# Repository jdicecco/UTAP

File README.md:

# UTAP
Undersea Technology Apprentice Program Python code

Program requires modules from the Adafruit CircuitPython libraries.  Also incorporates a snippet from the joystick.py interface modified to be Python3 compatible.

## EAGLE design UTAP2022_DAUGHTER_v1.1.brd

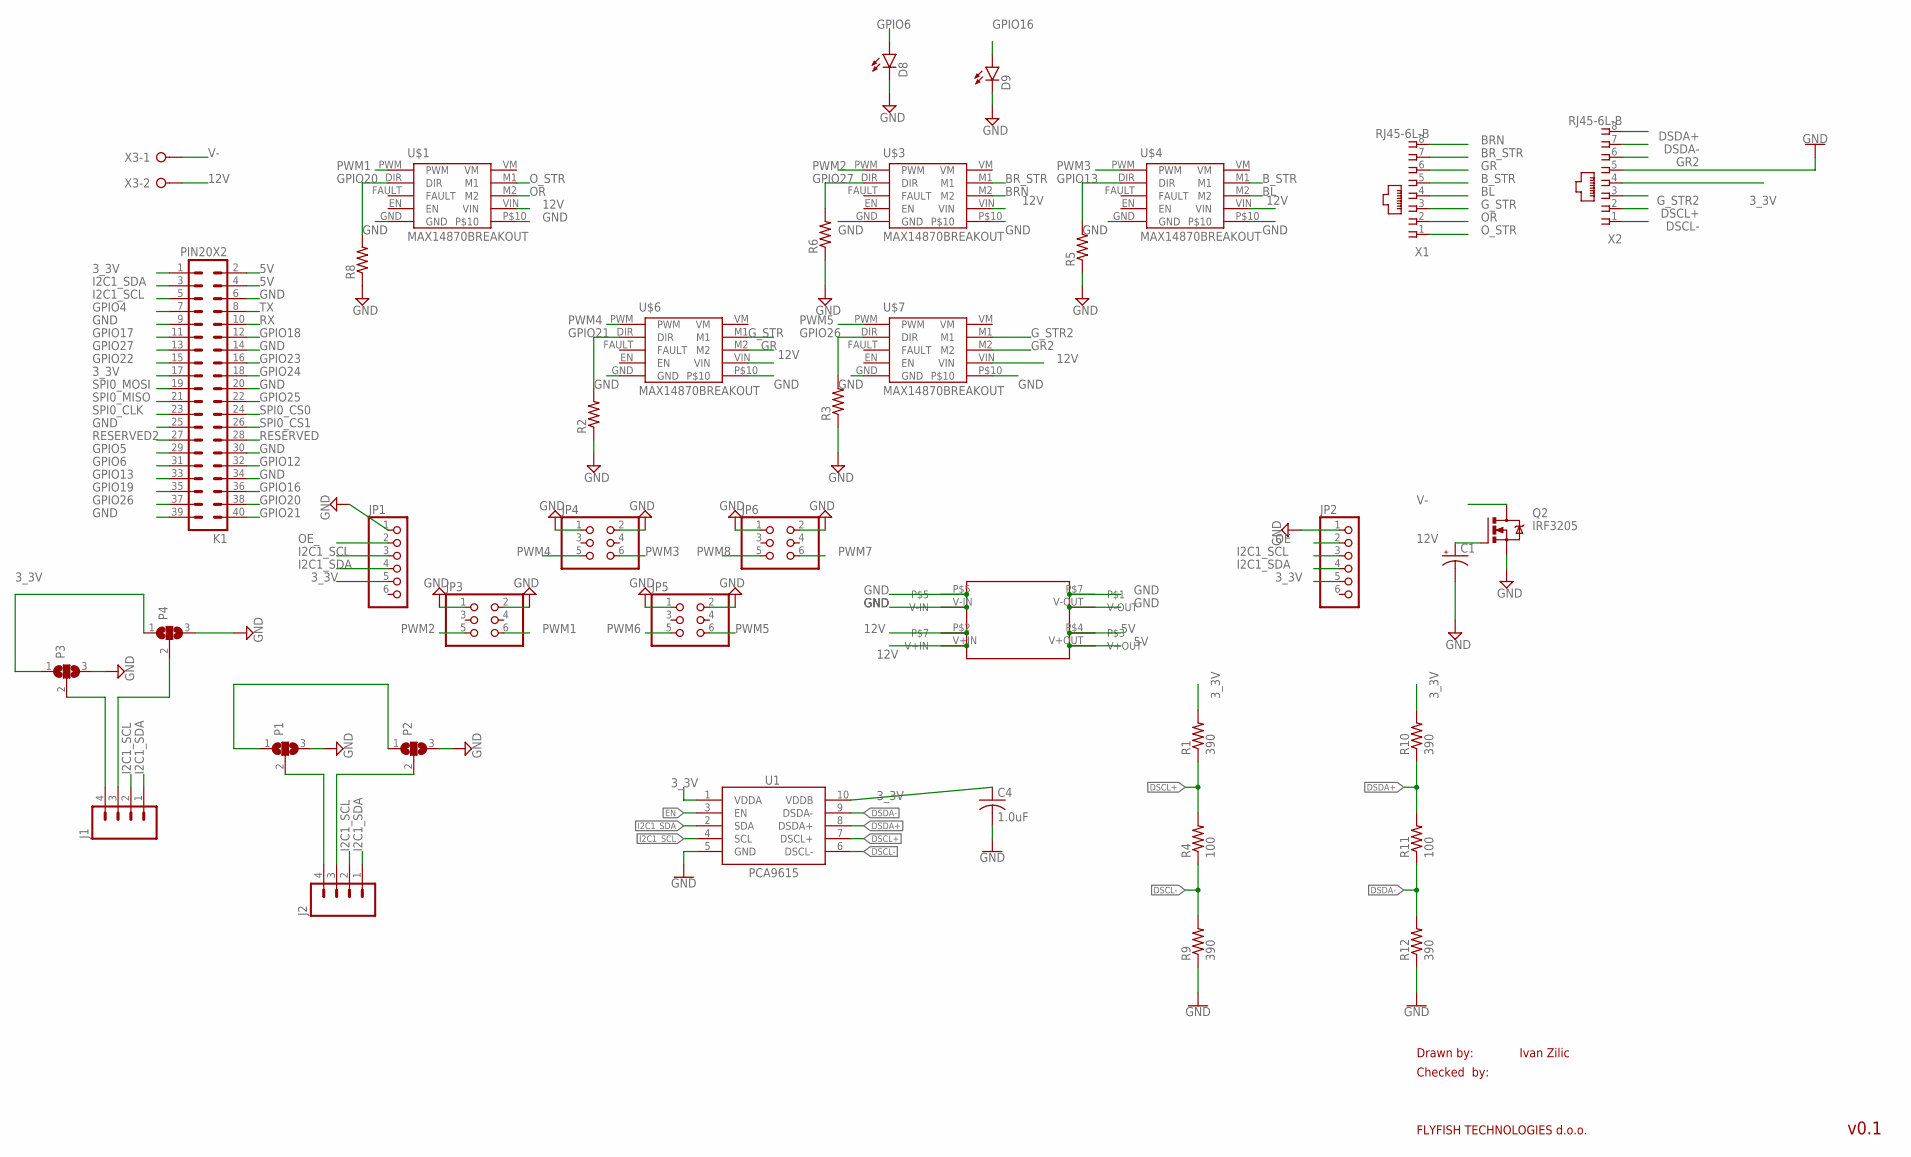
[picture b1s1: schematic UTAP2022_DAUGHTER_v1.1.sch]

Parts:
C1: CAP_POLPTH1; CPOL-RADIAL-100UF-25V
C4: 1.0uF; C050-024X044
D8, D9: LED5MM
J1, J2: M04PTH; 1X04
JP1, JP2: PINHD-1X6; 1X06
JP3, JP4, JP5, JP6: PINHD-2X3; 2X03
K1: PIN20X2; PIN_20X2
P1, P2, P3, P4: SJ2W; SJ_2
Q2: IRF3205; TO220BV
R1, R9, R10, R12: 390; 0204/7
R2, R3, R5, R6, R8: R-US_0204/7; 0204/7
R4, R11: 100; 0204/7
U1: PCA9615; TSSOP10
U$1, U$3, U$4, U$6, U$7: MAX14870BREAKOUT; MAX14870_BREAKOUT
U$9: MP1584EN; BUCK_CONV
X1, X2: RJ45-6L-B; RJ45-NO-SHIELD
X3: W237-02P; W237-132

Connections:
3_3V: C4.1, JP1.5, JP2.5, K1.1, K1.17, P1.1, P2.1, P3.1, P4.1, R1.2, R10.2, U1.1 (VDDA), U1.10 (VDDB), X2.4
5V: K1.2, K1.4, U$9.P$4, U$9.V+OUT
12V: C1.1 (+), Q2.G, U$1.VIN, U$3.VIN, U$4.VIN, U$6.VIN, U$7.VIN, U$9.P$2, U$9.V+IN, X3.2
BL: U$4.M2, X1.4
BRN: U$3.M2, X1.8
BR_STR: U$3.M1, X1.7
B_STR: U$4.M1, X1.5
DSCL+: R1.1, R4.2, U1.7 (DSCL+), X2.2
DSCL-: R4.1, R9.2, U1.6 (DSCL-), X2.1
DSDA+: R10.1, R11.2, U1.8 (DSDA+), X2.8
DSDA-: R11.1, R12.2, U1.9 (DSDA-), X2.7
EN: U1.3 (EN)
GND: C1.2 (-), C4.2, D8.K (C), D9.K (C), JP1.1, JP2.1, JP3.1, JP3.2, JP4.1, JP4.2, JP5.1, JP5.2, JP6.1, JP6.2, K1.6, K1.9, K1.14, K1.20, K1.25, K1.30, K1.34, K1.39, P1.3, P2.3, P3.3, P4.3, Q2.S, R2.1, R3.1, R5.1, R6.1, R8.1, R9.1, R12.1, U1.5 (GND), U$1.GND, U$1.P$10, U$3.GND, U$3.P$10, U$4.GND, U$4.P$10, U$6.GND, U$6.P$10, U$7.GND, U$7.P$10, U$9.P$5, U$9.P$7, U$9.V-IN, U$9.V-OUT, X2.5
GPIO4: K1.7
GPIO5: K1.29
GPIO6: D8.A, K1.31
GPIO12: K1.32
GPIO13: K1.33, R5.2, U$4.DIR
GPIO16: D9.A, K1.36
GPIO17: K1.11
GPIO18: K1.12
GPIO19: K1.35
GPIO20: K1.38, R8.2, U$1.DIR
GPIO21: K1.40, R2.2, U$6.DIR
GPIO22: K1.15
GPIO23: K1.16
GPIO24: K1.18
GPIO25: K1.22
GPIO26: K1.37, R3.2, U$7.DIR
GPIO27: K1.13, R6.2, U$3.DIR
GR: U$6.M2, X1.6
GR2: U$7.M2, X2.6
G_STR: U$6.M1, X1.3
G_STR2: U$7.M1, X2.3
I2C1_SCL: J1.2, J2.2, JP1.3, JP2.3, K1.5, U1.4 (SCL)
I2C1_SDA: J1.1, J2.1, JP1.4, JP2.4, K1.3, U1.2 (SDA)
unnamed: J1.4, P3.2
unnamed: J1.3, P4.2
unnamed: J2.4, P1.2
unnamed: J2.3, P2.2
OE: JP2.2
OE_: JP1.2
OR: U$1.M2, X1.2
O_STR: U$1.M1, X1.1
PWM1: JP3.6, U$1.PWM
PWM2: JP3.5, U$3.PWM
PWM3: JP4.6, U$4.PWM
PWM4: JP4.5, U$6.PWM
PWM5: JP5.6, U$7.PWM
PWM6: JP5.5
PWM7: JP6.6
PWM8: JP6.5
RESERVED: K1.28
RESERVED2: K1.27
RX: K1.10
SPI0_CLK: K1.23
SPI0_CS0: K1.24
SPI0_CS1: K1.26
SPI0_MISO: K1.21
SPI0_MOSI: K1.19
TX: K1.8
V-: Q2.D, X3.1

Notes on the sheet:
Drawn by:
Checked by:
FLYFISH TECHNOLOGIES d.o.o.
Ivan Zilic
v0.1

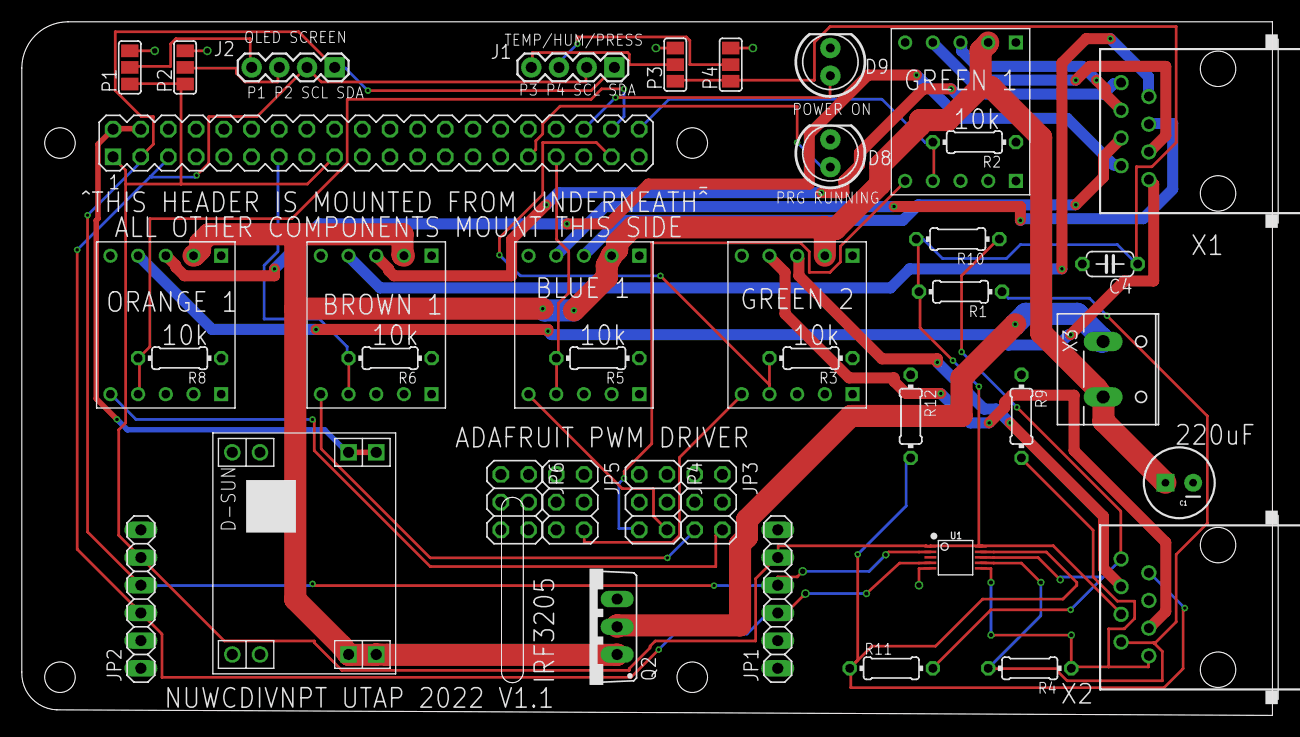
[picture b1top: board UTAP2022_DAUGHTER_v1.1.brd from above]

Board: 2 copper layers, 115.2 x 63.6 mm, 39 parts (0 on the bottom side), 37 nets.

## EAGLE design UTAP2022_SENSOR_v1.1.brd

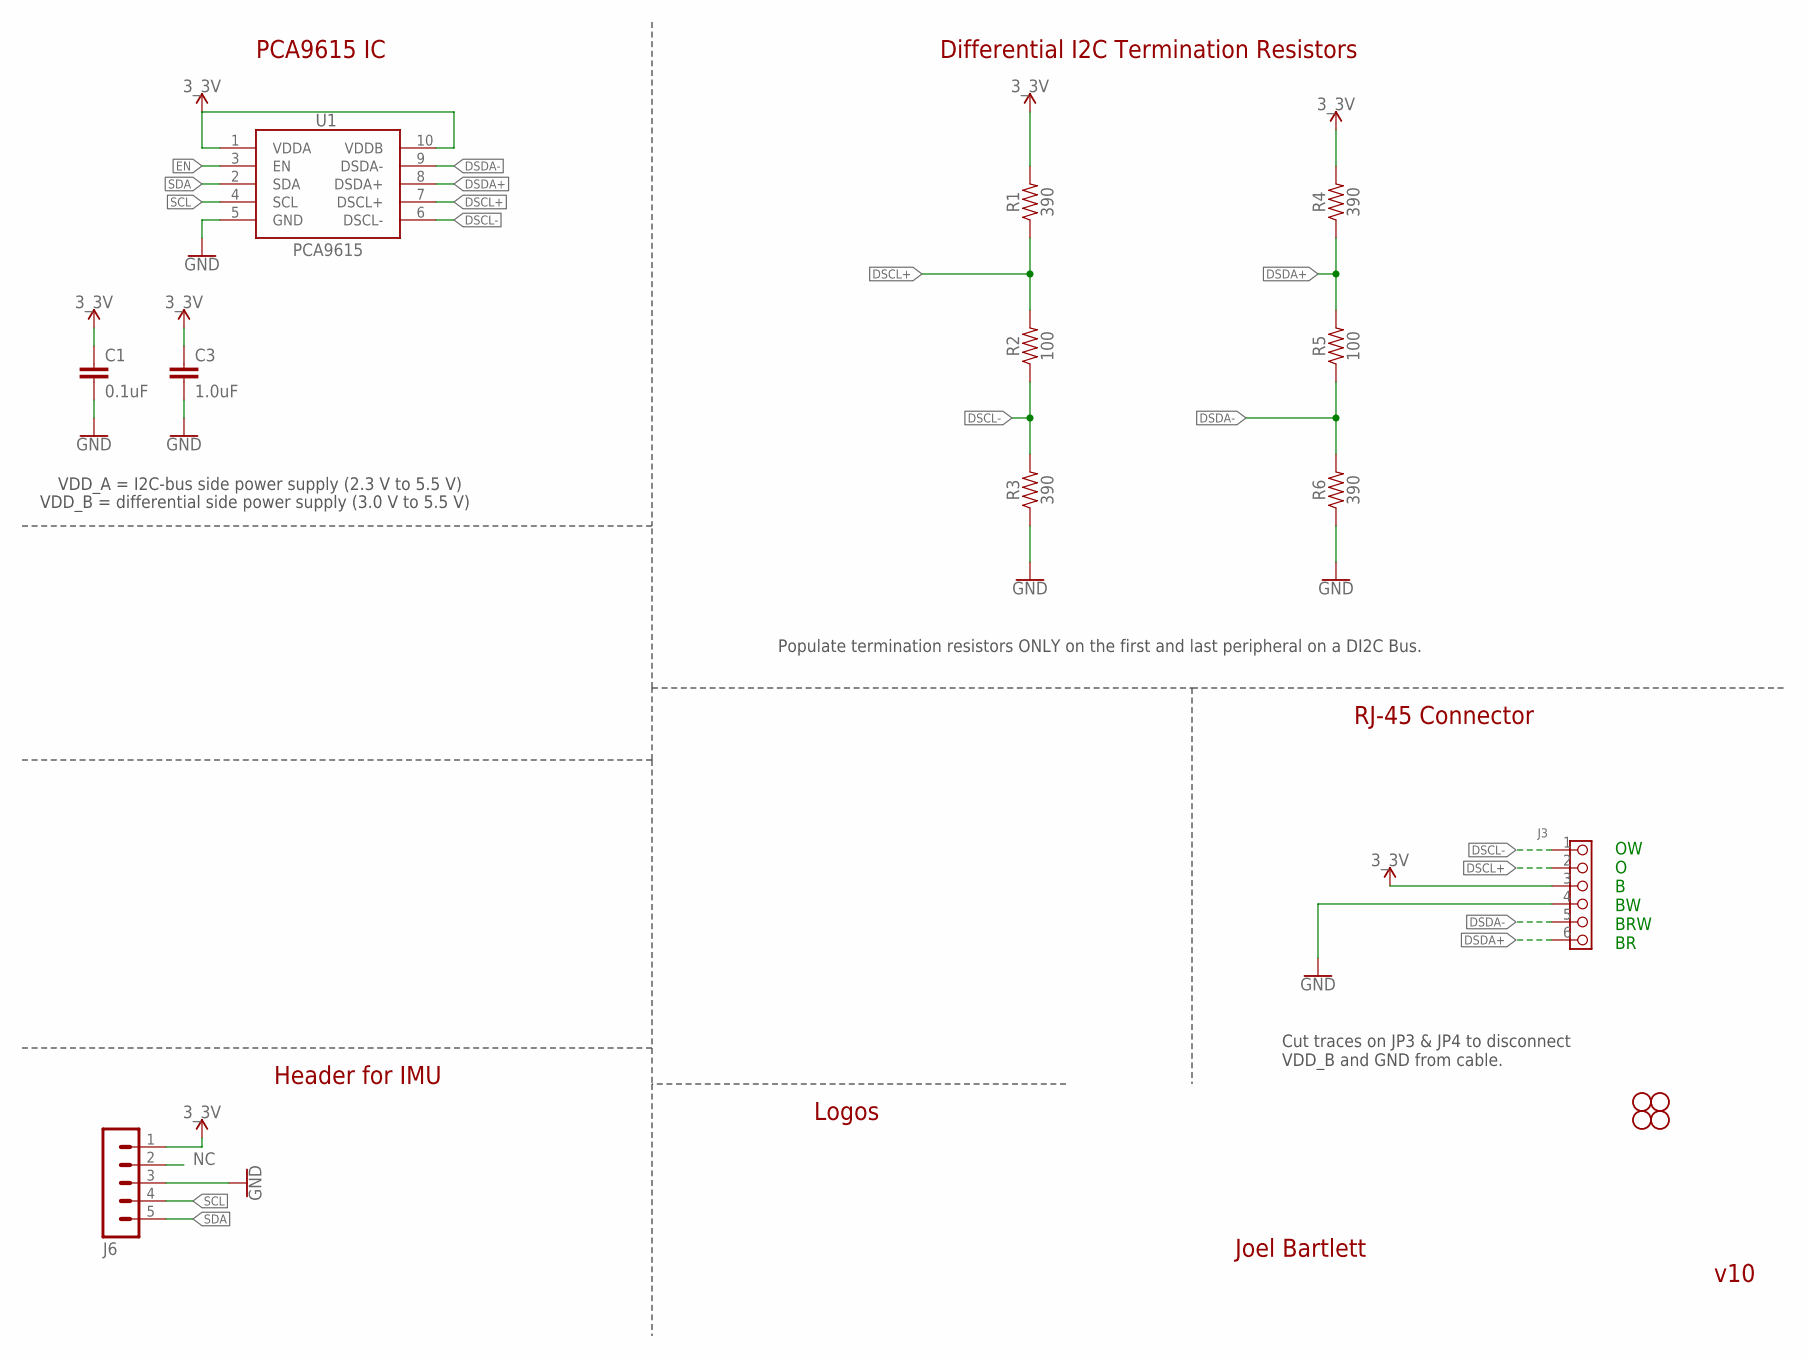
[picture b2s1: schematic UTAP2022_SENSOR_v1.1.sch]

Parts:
C1: 0.1uF; 0603
C3: 1.0uF; 0603
H1, H2, H3, H4: STAND-OFF
J3: CONNECTOR_HEADER-6P-55/35MIL; CONNECTOR_6P-2.54-55/35MIL
J6: MA05-1
R1, R3, R4, R6: 390; 0603
R2, R5: 100; 0603
U1: PCA9615; TSSOP10

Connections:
DSCL+: J3.2, R1.1, R2.2, U1.7 (DSCL+)
DSCL-: J3.1, R2.1, R3.2, U1.6 (DSCL-)
DSDA+: J3.6, R4.1, R5.2, U1.8 (DSDA+)
DSDA-: J3.5, R5.1, R6.2, U1.9 (DSDA-)
EN: U1.3 (EN)
GND: C1.2, C3.2, J3.4, J6.3, R3.1, R6.1, U1.5 (GND)
NC: J6.2
SCL: J6.4, U1.4 (SCL)
SDA: J6.5, U1.2 (SDA)
VDD_A: C1.1, C3.1, J3.3, J6.1, R1.2, R4.2, U1.1 (VDDA), U1.10 (VDDB)

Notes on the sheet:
Joel Bartlett
PCA9615 IC
v10
Header for IMU
RJ-45 Connector
Logos
Differential I2C Termination Resistors
Populate termination resistors ONLY on the first and last peripheral on a DI2C Bus.
VDD_A = I2C-bus side power supply (2.3 V to 5.5 V)
VDD_B = differential side power supply (3.0 V to 5.5 V)
Cut traces on JP3 & JP4 to disconnect VDD_B and GND from cable.
OW O B BW BRW BR

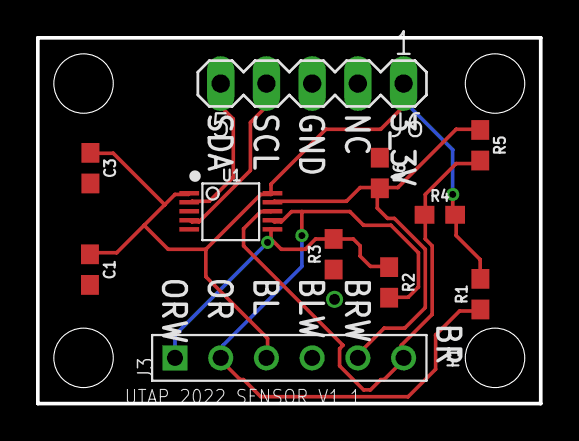
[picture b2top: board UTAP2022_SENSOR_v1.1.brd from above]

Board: 2 copper layers, 27.9 x 20.3 mm, 15 parts (0 on the bottom side), 8 nets.

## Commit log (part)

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2021-07-27 Rename UTAP_2020.py to UTAP_2021.py
2024-01-12 Rename UTAP_2023_RPi.pdf to UTAP_2023_RPi_MANUAL.pdf
2024-07-05 Rename UTAP_2023_RPi_MANUAL.pdf to UTAP_RPi_MANUAL.pdf
2024-07-05 Rename UTAP_2022_EngReport_template.doc to UTAP_EngReport_template.doc

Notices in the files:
parts and their libraries:
SparkFun-Passives: Licensing: Creative Commons ShareAlike 4.0 International - https://creativecommons.org/licenses/by-sa/4.0
